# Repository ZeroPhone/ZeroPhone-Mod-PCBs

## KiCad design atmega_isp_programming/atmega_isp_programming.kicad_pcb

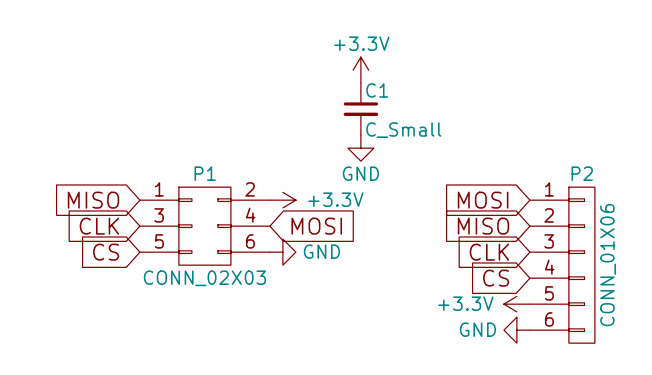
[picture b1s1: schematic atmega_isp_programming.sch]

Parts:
C1: C_Small; C_0805_HandSoldering
P1: CONN_02X03; Pin_Header_Straight_2x03_Pitch2.54mm
P2: CONN_01X06; Pin_Header_Straight_1x06_Pitch2.54mm

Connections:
+3V3: C1.1, P1.2, P2.5
CLK: P1.3, P2.3
CS: P1.5, P2.4
GND: C1.2, P1.6, P2.6
MISO: P1.1, P2.2
MOSI: P1.4, P2.1

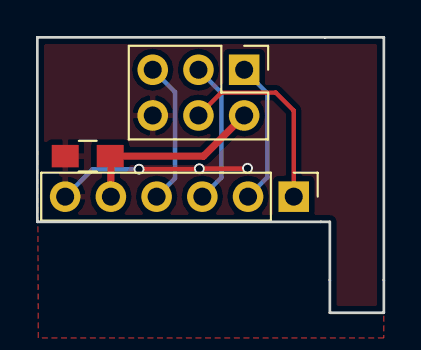
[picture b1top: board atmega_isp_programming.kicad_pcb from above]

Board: 2 copper layers, 19.2 x 15.3 mm, 3 parts (0 on the bottom side), 6 nets.

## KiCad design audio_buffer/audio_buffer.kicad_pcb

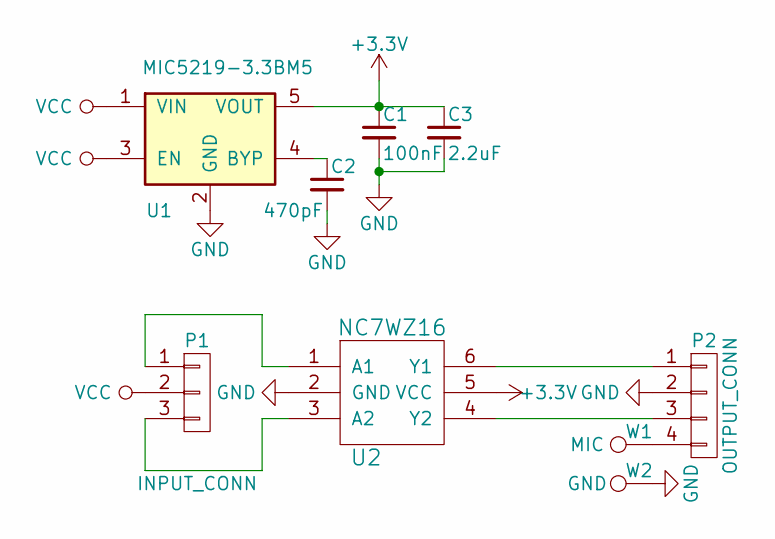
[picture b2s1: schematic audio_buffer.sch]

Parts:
C1: 100nF; C_0603_HandSoldering
C2: 470pF; C_0603_HandSoldering
C3: 2.2uF; C_0603_HandSoldering
P1: INPUT_CONN; Pin_Header_Straight_1x03_Pitch2.54mm
P2: OUTPUT_CONN; Pin_Header_Straight_1x04_Pitch2.54mm
U1: MIC5219-3.3BM5; SOT-23-5
U2: NC7WZ16; SOT-363_SC-70-6
W1: MIC; Measurement_Point_Round-SMD-Pad_Small
W2: GND; Measurement_Point_Round-SMD-Pad_Small

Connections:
+3V3: C1.1, C3.1, U1.5 (VOUT), U2.5 (VCC)
GND: C1.2, C2.2, C3.2, P2.2, U1.2 (GND), U2.2 (GND), W2.1
unnamed: C2.1, U1.4 (BYP)
unnamed: P1.1, U2.1 (A1)
unnamed: P1.3, U2.3 (A2)
unnamed: P2.1, U2.6 (Y1)
unnamed: P2.3, U2.4 (Y2)
unnamed: P2.4, W1.1
VCC: P1.2, U1.1 (VIN), U1.3 (EN)

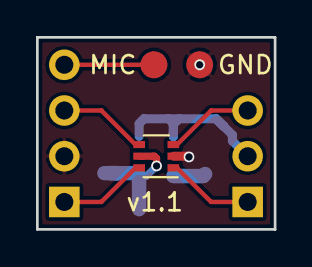
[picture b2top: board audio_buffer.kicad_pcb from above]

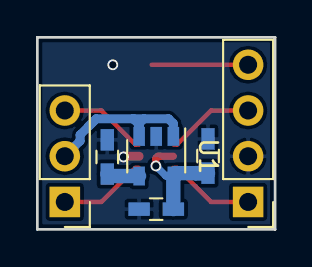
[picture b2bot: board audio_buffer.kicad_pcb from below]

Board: 2 copper layers, 13.2 x 10.7 mm, 9 parts (6 on the bottom side), 9 nets.

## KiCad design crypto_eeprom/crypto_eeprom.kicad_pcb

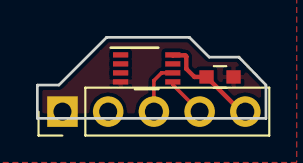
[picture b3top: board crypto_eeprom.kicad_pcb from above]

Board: 2 copper layers, 12.7 x 4.5 mm, 3 parts (0 on the bottom side), 4 nets.

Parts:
C1: C; C_0603
J1: EXPANSION_BOTTOM; Pin_Header_Straight_1x05_Pitch2.54mm
U1: ATSHA204A; DFN-8_3x2mm_Pitch0.5mm

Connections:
GND: C1.2, J1.1, U1.4
SCL: J1.3, U1.6
SDA: J1.4, U1.5
VCC: C1.1, J1.5, U1.8

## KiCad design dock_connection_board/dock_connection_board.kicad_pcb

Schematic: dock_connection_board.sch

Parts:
C1: 100nF; C_0805_HandSoldering
J1: USBO; Pin_Header_Straight_1x05_Pitch2.54mm
J2: USBI; Pin_Header_Straight_1x04_Pitch2.54mm
J3: CHG; TerminalBlock_bornier-2_P5.08mm
J4: I2CI; Pin_Header_Straight_1x05_Pitch2.54mm
J5: AUXI; Pin_Header_Straight_1x03_Pitch2.54mm
J6: ANI; Pin_Header_Straight_1x03_Pitch2.54mm
J7: I2CO; Pin_Header_Straight_1x05_Pitch2.54mm
JP1: CUVCC; GS2
JP2: ZUVCC; GS2
JP3: ADC; GS2
R1: 10K; R_0805_HandSoldering
TP1: WP; Measurement_Point_Round-SMD-Pad_Small
U1: 24LC32; SOIC-8_3.9x4.9mm_Pitch1.27mm

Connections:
+3V3: C1.1, J4.1, J6.3, J7.1, R1.2, U1.8 (VCC)
+5V: J5.1, JP1.1
ADC: J6.2, JP3.1
CHG: J1.5, J3.1, J5.3, JP1.2
D+: J1.3, J2.3
D-: J1.2, J2.2
GND: C1.2, J1.4, J2.4, J3.2, J4.5, J6.1, J7.5, U1.1 (A0), U1.2 (A1), U1.3 (A2), U1.4 (GND)
GPIO: J4.4, J7.4
unnamed: J1.1, JP2.1
unnamed: J2.1, JP2.2
unnamed: J5.2, JP3.2
unnamed: R1.1, TP1.1, U1.7 (WP)
SCL: J4.3, J7.3, U1.6 (SCL)
SDA: J4.2, J7.2, U1.5 (SDA)

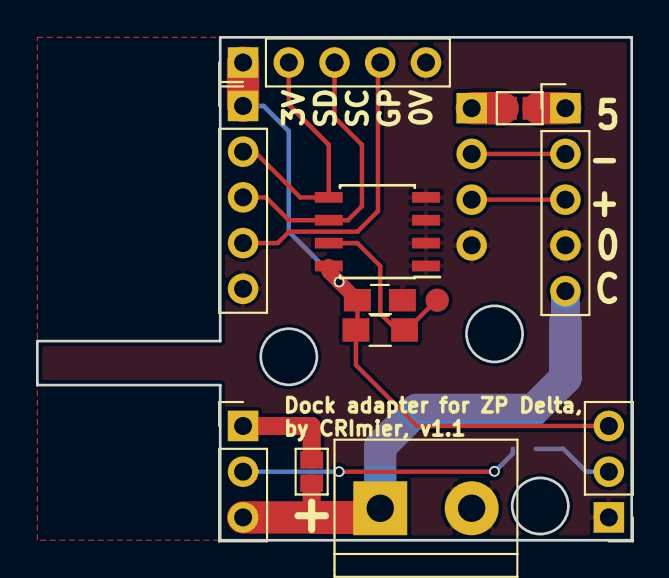
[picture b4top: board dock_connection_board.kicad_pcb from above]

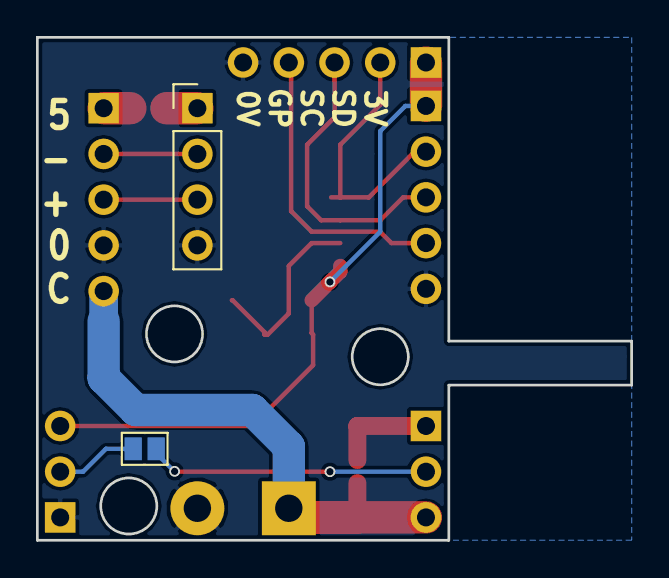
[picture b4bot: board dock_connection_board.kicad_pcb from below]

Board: 2 copper layers, 33.0 x 27.9 mm, 14 parts (2 on the bottom side), 14 nets.

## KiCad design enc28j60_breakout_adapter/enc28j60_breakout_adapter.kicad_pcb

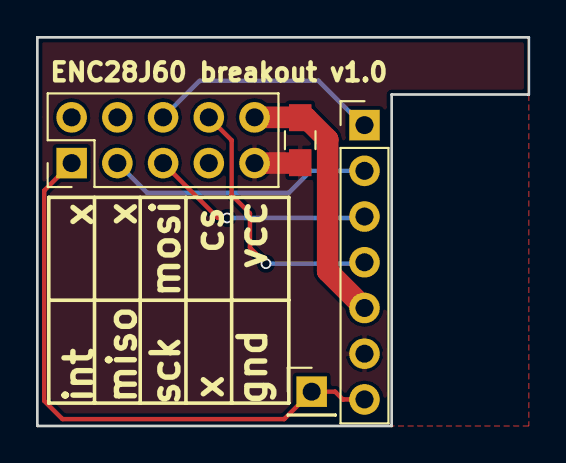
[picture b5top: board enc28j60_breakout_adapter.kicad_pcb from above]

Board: 2 copper layers, 27.3 x 21.6 mm, 4 parts (0 on the bottom side), 7 nets.

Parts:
C1: C_Small; C_0805_HandSoldering
J1: CONN_02X05; Pin_Header_Straight_2x05_Pitch2.54mm
J2: CONN_01X07; Pin_Header_Straight_1x07_Pitch2.54mm
J3: INT; Pin_Header_Straight_1x01_Pitch2.54mm

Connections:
+3V3: C1.1, J1.10, J2.5
CS: J1.8, J2.4
GND: C1.2, J1.9, J2.6
INT: J1.1, J2.7, J3.1
MISO: J1.3, J2.2
MOSI: J1.6, J2.1
SCK: J1.5, J2.3

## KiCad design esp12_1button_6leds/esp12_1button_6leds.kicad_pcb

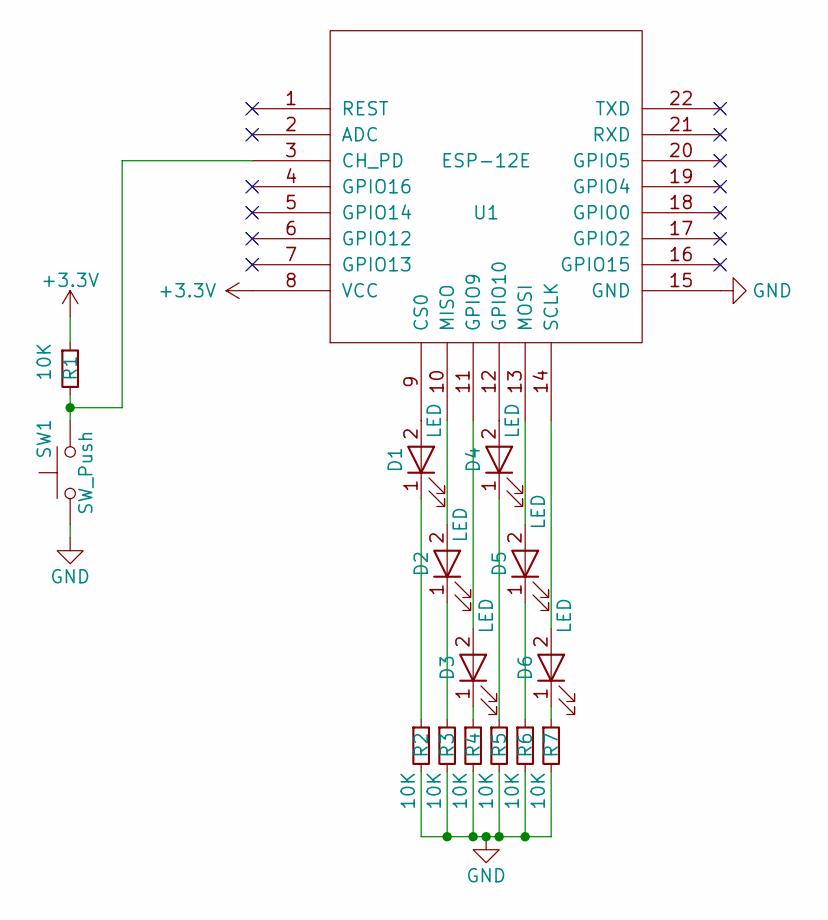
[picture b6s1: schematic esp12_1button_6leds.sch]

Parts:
D1, D2, D3, D4, D5, D6: LED; D_0805
R1, R2, R3, R4, R5, R6, R7: 10K; R_0603_HandSoldering
SW1: SW_Push; SW_SPST_EVQP7C
U1: ESP-12E; ESP12_BASE

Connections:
+3V3: R1.1, U1.8 (VCC)
GND: R2.2, R3.2, R4.2, R5.2, R6.2, R7.2, SW1.1, U1.15 (GND)
unnamed: D1.1 (K), R2.1
unnamed: D1.2 (A), U1.9 (CS0)
unnamed: D2.1 (K), R3.1
unnamed: D2.2 (A), U1.10 (MISO)
unnamed: D3.1 (K), R4.1
unnamed: D3.2 (A), U1.11 (GPIO9)
unnamed: D4.1 (K), R5.1
unnamed: D4.2 (A), U1.12 (GPIO10)
unnamed: D5.1 (K), R6.1
unnamed: D5.2 (A), U1.13 (MOSI)
unnamed: D6.1 (K), R7.1
unnamed: D6.2 (A), U1.14 (SCLK)
unnamed: R1.2, SW1.2, U1.3 (CH_PD)

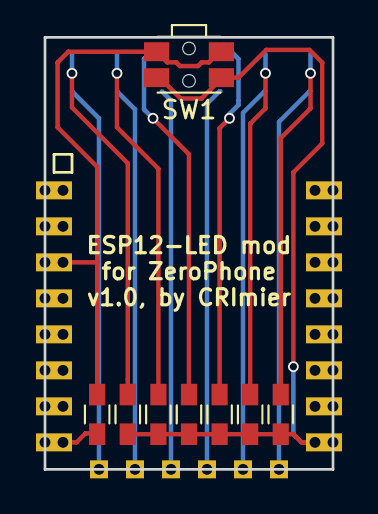
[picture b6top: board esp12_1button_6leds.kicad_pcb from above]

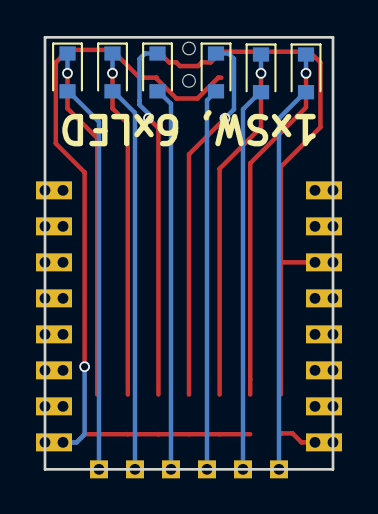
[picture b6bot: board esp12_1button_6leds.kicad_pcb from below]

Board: 2 copper layers, 16.0 x 24.0 mm, 15 parts (6 on the bottom side), 15 nets.

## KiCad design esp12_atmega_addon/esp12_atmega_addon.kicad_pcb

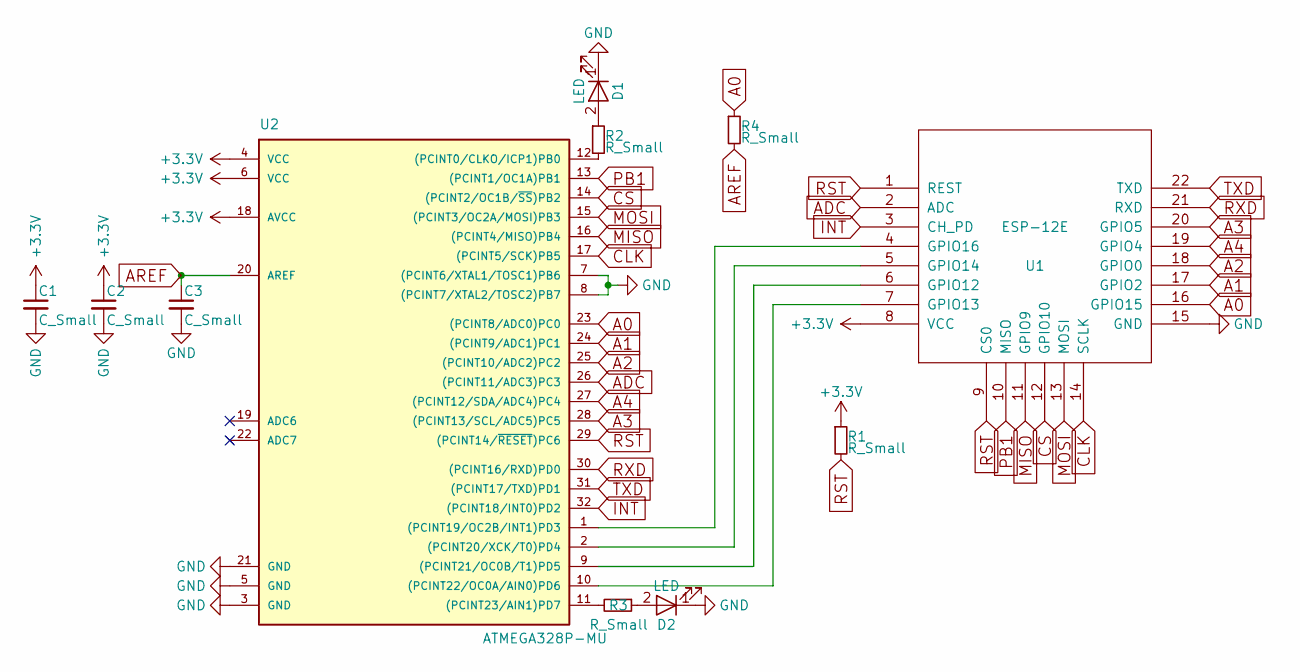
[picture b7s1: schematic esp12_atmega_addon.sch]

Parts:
C1, C2, C3: C_Small; C_0603
D1, D2: LED; LED_0805
R1, R2, R3, R4: R_Small; R_0603
U1: ESP-12E; ESP12_BASE
U2: ATMEGA328P-MU; QFN-32-1EP_5x5mm_Pitch0.5mm

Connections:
+3V3: C1.1, C2.1, R1.1, U1.8 (VCC), U2.4 (VCC), U2.6 (VCC), U2.18 (AVCC)
A0: R4.1, U1.16 (GPIO15), U2.23 ((PCINT8/ADC0)PC0)
A1: U1.17 (GPIO2), U2.24 ((PCINT9/ADC1)PC1)
A2: U1.18 (GPIO0), U2.25 ((PCINT10/ADC2)PC2)
A3: U1.20 (GPIO5), U2.28 ((PCINT13/SCL/ADC5)PC5)
A4: U1.19 (GPIO4), U2.27 ((PCINT12/SDA/ADC4)PC4)
ADC: U1.2 (ADC), U2.26 ((PCINT11/ADC3)PC3)
AREF: C3.1, R4.2, U2.20 (AREF)
CLK: U1.14 (SCLK), U2.17 ((PCINT5/SCK)PB5)
CS: U1.12 (GPIO10), U2.14 ((PCINT2/OC1B/~SS~)PB2)
GND: C1.2, C2.2, C3.2, D1.1 (K), D2.1 (K), U1.15 (GND), U2.3 (GND), U2.5 (GND), U2.7 ((PCINT6/XTAL1/TOSC1)PB6), U2.8 ((PCINT7/XTAL2/TOSC2)PB7), U2.21 (GND), U2.33
INT: U1.3 (CH_PD), U2.32 ((PCINT18/INT0)PD2)
MISO: U1.11 (GPIO9), U2.16 ((PCINT4/MISO)PB4)
MOSI: U1.13 (MOSI), U2.15 ((PCINT3/OC2A/MOSI)PB3)
unnamed: D1.2 (A), R2.1
unnamed: D2.2 (A), R3.1
unnamed: R2.2, U2.12 ((PCINT0/CLKO/ICP1)PB0)
unnamed: R3.2, U2.11 ((PCINT23/AIN1)PD7)
unnamed: U1.4 (GPIO16), U2.1 ((PCINT19/OC2B/INT1)PD3)
unnamed: U1.5 (GPIO14), U2.2 ((PCINT20/XCK/T0)PD4)
unnamed: U1.6 (GPIO12), U2.9 ((PCINT21/OC0B/T1)PD5)
unnamed: U1.7 (GPIO13), U2.10 ((PCINT22/OC0A/AIN0)PD6)
PB1: U1.10 (MISO), U2.13 ((PCINT1/OC1A)PB1)
RST: R1.2, U1.1 (REST), U1.9 (CS0), U2.29 ((PCINT14/~RESET~)PC6)
RXD: U1.21 (RXD), U2.30 ((PCINT16/RXD)PD0)
TXD: U1.22 (TXD), U2.31 ((PCINT17/TXD)PD1)

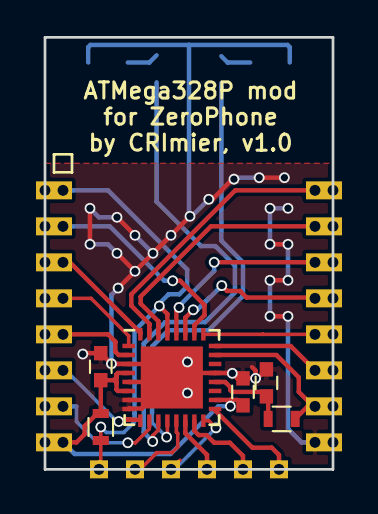
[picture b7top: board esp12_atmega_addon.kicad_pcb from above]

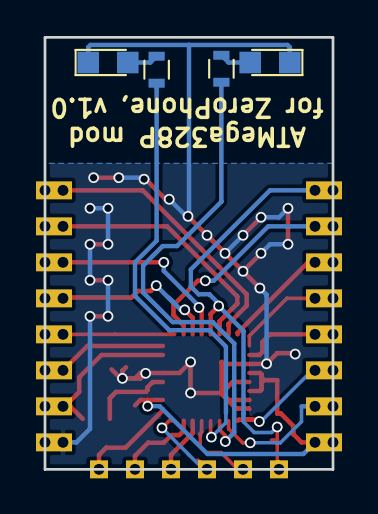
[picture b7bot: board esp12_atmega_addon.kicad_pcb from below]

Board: 2 copper layers, 16.0 x 24.0 mm, 11 parts (4 on the bottom side), 26 nets.
